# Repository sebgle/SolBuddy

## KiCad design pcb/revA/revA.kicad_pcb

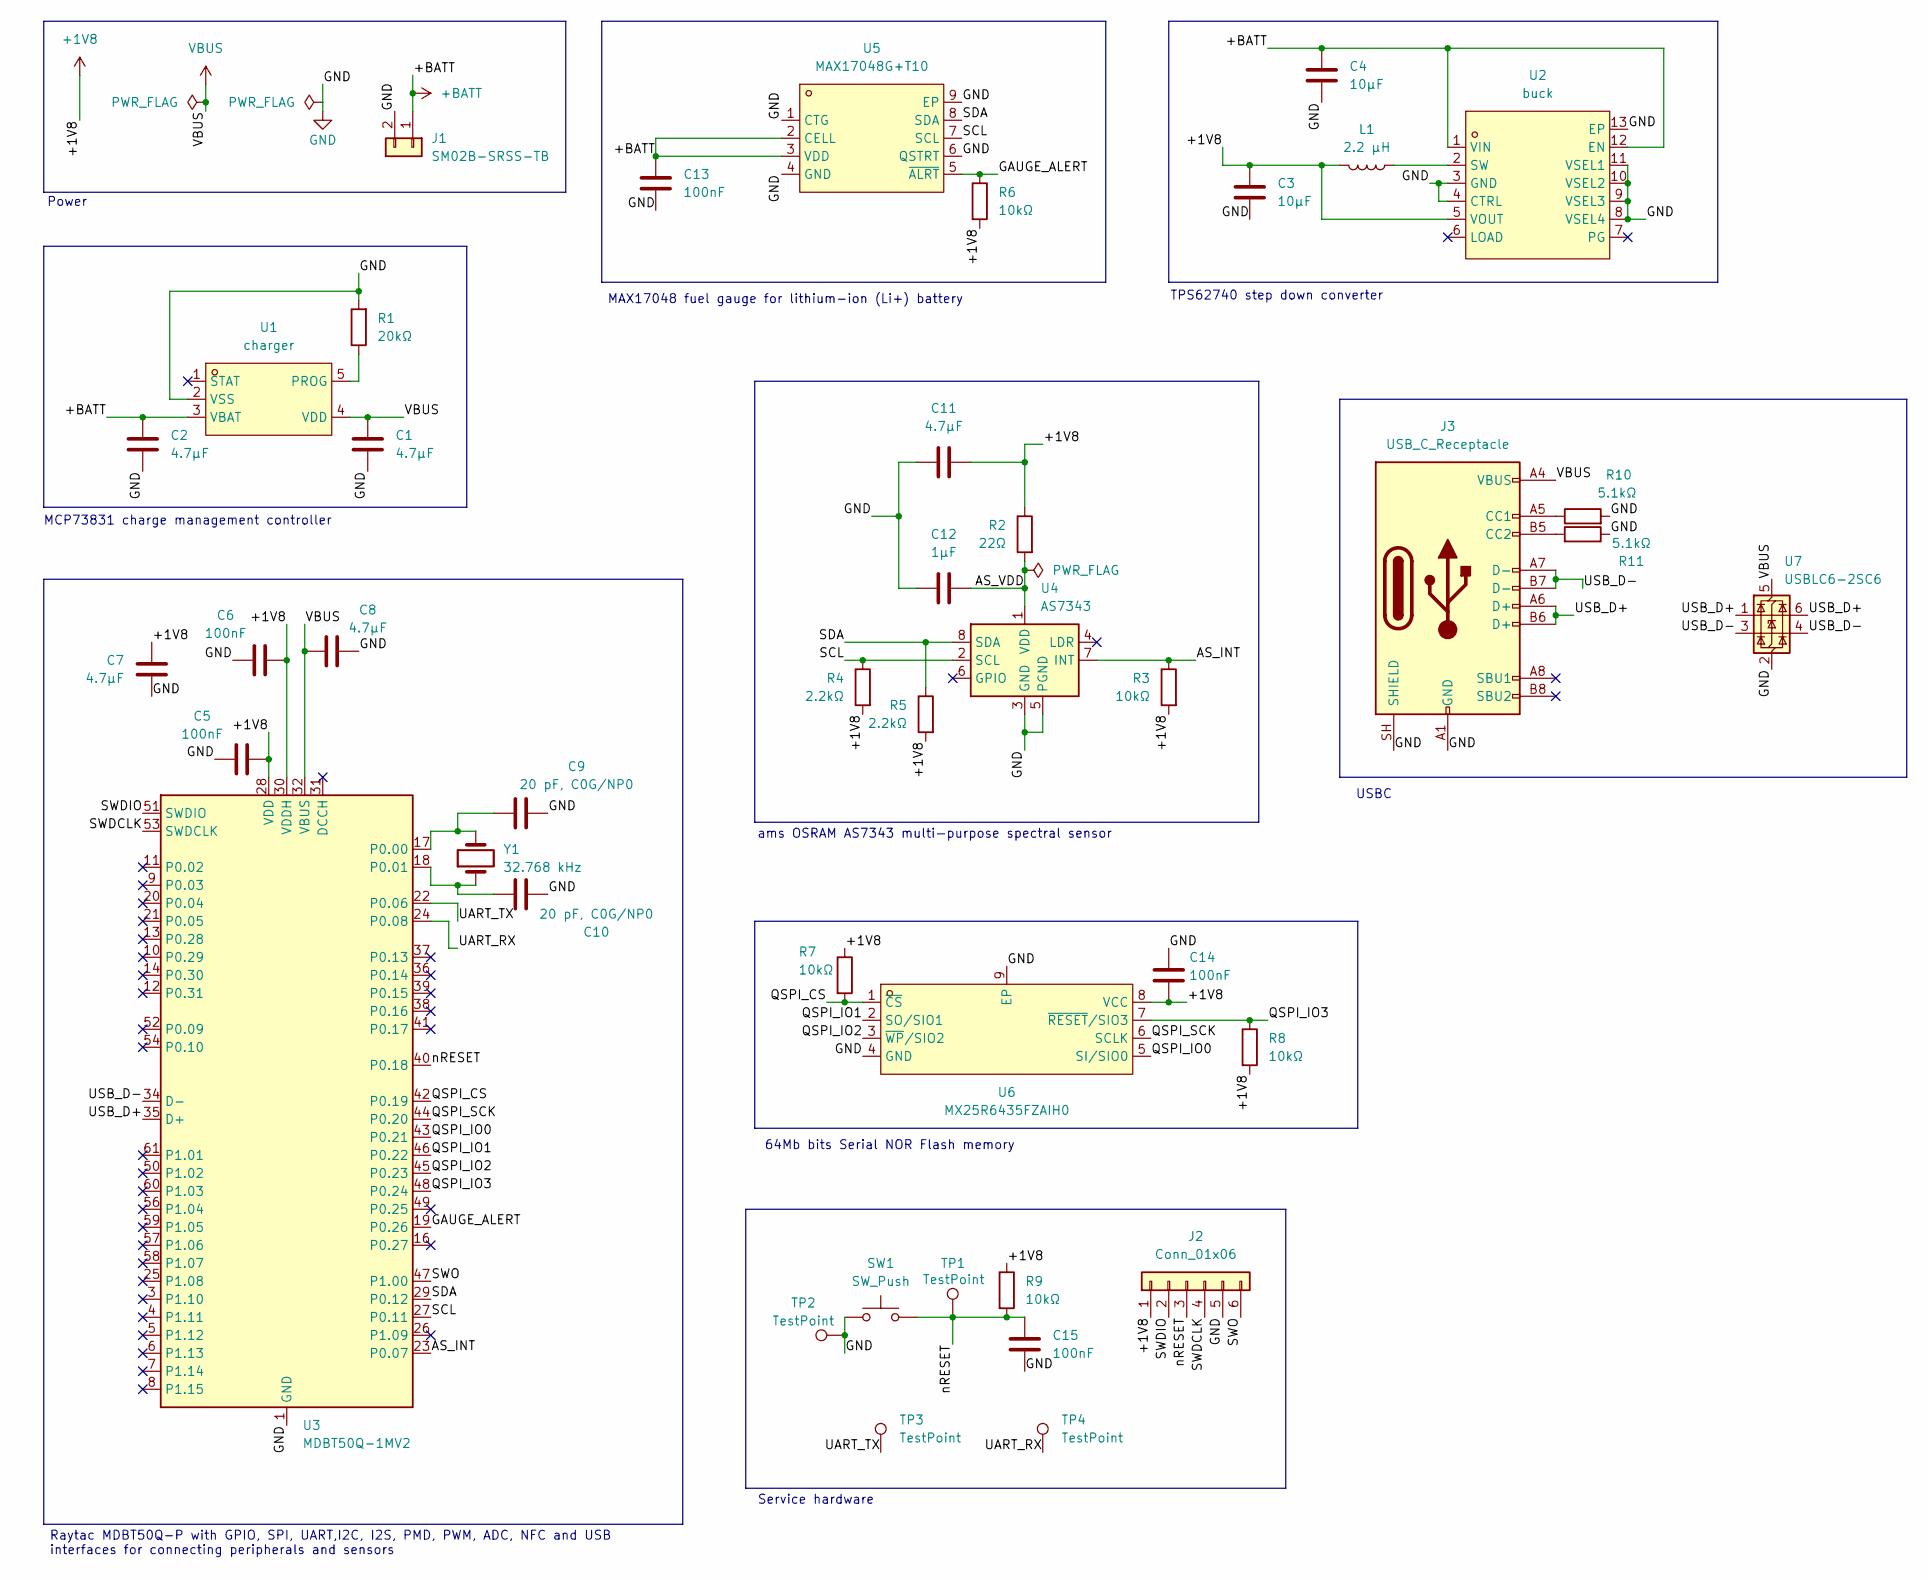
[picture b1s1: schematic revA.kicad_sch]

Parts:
C1, C2, C7, C8, C11: 4.7µF; C_0603_1608Metric; LCSC C19666
C3, C4: 10µF; C_0603_1608Metric; LCSC C96446
C5, C6, C13, C14, C15: 100nF; C_0402_1005Metric; LCSC C1525
C9, C10: 20 pF, C0G/NP0; C_0402_1005Metric; LCSC C1554
C12: 1µF; C_0402_1005Metric; LCSC C52923
J1: SM02B-SRSS-TB; JST_PH_S2B-PH-SM4-TB_1x02-1MP_P2.00mm_Horizontal; LCSC C295747
J2: Conn_01x06; Tag-Connect_TC2030-IDC-NL_2x03_P1.27mm_Vertical
J3: USB_C_Receptacle; USB_C_Receptacle_HRO_TYPE-C-31-M-12; LCSC C165948
L1: 2.2 µH; IND-SMD_L2.0-W1.6-B; LCSC C5832344
R1: 20kΩ; R_0402_1005Metric; LCSC C25765
R2: 22Ω; R_0402_1005Metric; LCSC C25092
R3, R6, R7, R8, R9: 10kΩ; R_0402_1005Metric; LCSC C25744
R4, R5: 2.2kΩ; R_0402_1005Metric; LCSC C25879
R10, R11: 5.1kΩ; R_0402_1005Metric; LCSC C25905
SW1: SW_Push; SW-SMD_L3.9-W3.0-P4.45; LCSC C720477
TP1, TP2, TP3, TP4: TestPoint; TestPoint_Pad_D1.0mm
U1: charger; SOT-23-5_L3.0-W1.7-P0.95-LS2.8-BL; MPN MCP73831T-2ACI/OT; LCSC C424093
U2: buck; WSON-12_L3.0-W2.0-P0.50-BL-EP; MPN TPS62740DSSR; LCSC C128606
U3: MDBT50Q-1MV2; Raytac_MDBT50Q; LCSC C5118826
U4: AS7343; AMS_OLGA-8_2x3.1mm_P0.8mm; LCSC C19085986
U5: MAX17048G+T10; TDFN-8_L2.0-W2.0-P0.50-BL-EP1.2; MPN MAX17048G+T10; LCSC C2682616
U6: MX25R6435FZAIH0; USON-8_L4.0-W4.0-P0.80-BL-EP; MPN MX25R6435FZAIH0; LCSC C2802846
U7: USBLC6-2SC6; SOT-23-6; LCSC C7519
Y1: 32.768 kHz; Crystal_SMD_3215-2Pin_3.2x1.5mm; LCSC C130253

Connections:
+1V8: C3.1, C5.1, C6.2, C7.2, C11.1, C14.2, J2.1, L1.2, R2.1, R3.2, R4.2, R5.2, R6.2, R7.1, R8.2, R9.1, U2.5 (VOUT), U3.28 (VDD), U3.30 (VDDH), U6.8 (VCC)
+BATT: C2.1, C4.1, C13.1, J1.1, U1.3 (VBAT), U2.1 (VIN), U2.12 (EN), U5.2 (CELL), U5.3 (VDD)
/AS_INT: R3.1, U3.23 (P0.07), U4.7 (INT)
/AS_VDD: C12.1, R2.2, U4.1 (VDD)
/GAUGE_ALERT: R6.1, U3.19 (P0.26), U5.5 (~ALRT)
/QSPI_CS: R7.2, U3.42 (P0.19), U6.1 (~CS)
/QSPI_IO0: U3.43 (P0.21), U6.5 (SI/SIO0)
/QSPI_IO1: U3.46 (P0.22), U6.2 (SO/SIO1)
/QSPI_IO2: U3.45 (P0.23), U6.3 (~WP/SIO2)
/QSPI_IO3: R8.1, U3.48 (P0.24), U6.7 (~RESET/SIO3)
/QSPI_SCK: U3.44 (P0.20), U6.6 (SCLK)
/SCL: R4.1, U3.27 (P0.11), U4.2 (SCL), U5.7 (SCL)
/SDA: R5.1, U3.29 (P0.12), U4.8 (SDA), U5.8 (SDA)
/SWDCLK: J2.4, U3.53 (SWDCLK)
/SWDIO: J2.2, U3.51 (SWDIO)
/SWO: J2.6, U3.47 (P1.00)
/UART_RX: TP4.1 (1_1), U3.24 (P0.08)
/UART_TX: TP3.1 (1_1), U3.22 (P0.06)
/USB_D+: J3.A6 (D+), J3.B6 (D+), U3.35 (D+), U7.1 (I/O1), U7.6 (I/O1)
/USB_D-: J3.A7 (D-), J3.B7 (D-), U3.34 (D-), U7.3 (I/O2), U7.4 (I/O2)
/nRESET: C15.1, J2.3, R9.2, SW1.2, TP1.1 (1_1), U3.40 (P0.18)
GND: C1.2, C2.2, C3.2, C4.2, C5.2, C6.1, C7.1, C8.2, C9.2, C10.2, C11.2, C12.2, C13.2, C14.1, C15.2, J1.2, J2.5, J3.A1 (GND), J3.A12 (GND), J3.B1 (GND), J3.B12 (GND), J3.SH (SHIELD), R1.2, R10.2, R11.1, SW1.1, TP2.1 (1_1), U1.2 (VSS), U2.3 (GND), U2.4 (CTRL), U2.8 (VSEL4), U2.9 (VSEL3), U2.10 (VSEL2), U2.11 (VSEL1), U2.13 (EP), U3.1 (GND), U3.2 (GND), U3.15 (GND), U3.33 (GND), U3.55 (GND), U4.3 (GND), U4.5 (PGND), U5.1 (CTG), U5.4 (GND), U5.6 (QSTRT), U5.9 (EP), U6.4 (GND), U6.9 (EP), U7.2 (GND)
unnamed: J3.A5 (CC1), R10.1
unnamed: J3.B5 (CC2), R11.2
unnamed: R1.1, U1.5 (PROG)
unnamed: L1.1, U2.2 (SW)
unnamed: C9.1, U3.17 (P0.00), Y1.2
unnamed: C10.1, U3.18 (P0.01), Y1.1
VBUS: C1.1, C8.1, J3.A4 (VBUS), J3.A9 (VBUS), J3.B4 (VBUS), J3.B9 (VBUS), U1.4 (VDD), U3.32 (VBUS), U7.5 (VBUS)

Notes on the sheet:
64Mb bits Serial NOR Flash memory
MAX17048 fuel gauge for lithium-ion (Li+) battery
USBC
ams OSRAM AS7343 multi-purpose spectral sensor
Service hardware
Power
TPS62740 step down converter
MCP73831 charge management controller
Raytac MDBT50Q-P with GPIO, SPI, UART,I2C, I2S, PMD, PWM, ADC, NFC and USB interfaces for connecting peripherals and sensors

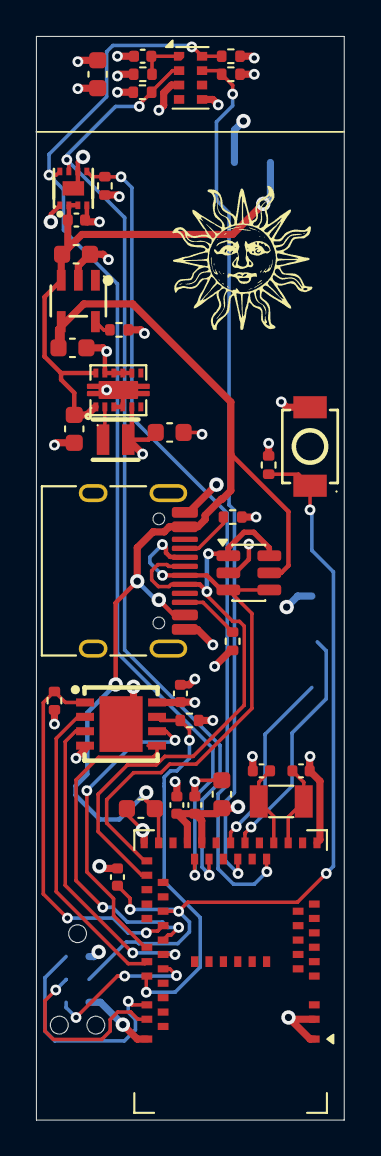
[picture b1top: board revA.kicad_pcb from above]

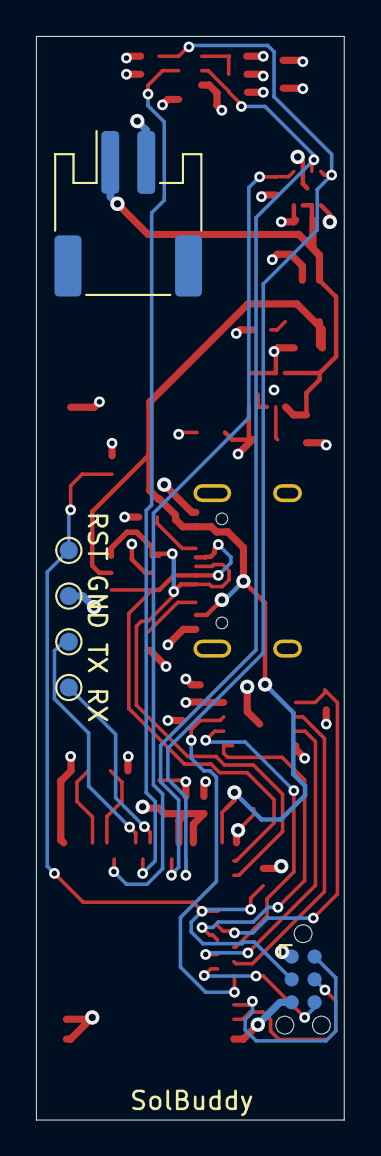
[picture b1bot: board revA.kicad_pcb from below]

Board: 4 copper layers, 17.1 x 60.2 mm, 43 parts (6 on the bottom side), 29 nets.
